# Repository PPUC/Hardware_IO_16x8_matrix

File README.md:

# Switch Matrix PCB for PPUC Project
This is the hardware for a 16x8 switch matrix card which was designed for the PPUC pinball project, but can be useful in other applications as well. The intentionally usecase is to connect an original equipped pinball playfield (including cable harness and diodes). Normally I'd prefer direct switches but if all the switches and cables and diodes are in place already, it is useful to connect the switch matrix directly. The board can also be used for 16 direct inputs and 8 low power signal-outputs (no matrix).  
It is designed for being low cost and functional for experimental use.  
Not everything is tested nor does it fulfill EMC or any other specifications.  
Use at your own risk!
To make use of anything of this project a basic understanding of electronics and programming is necessary. Nothing of it is "plug and play". I'm surely not liable for any damage to assemblies, pinball machines or even persons.

<!---
## Picture of the Board

-->

## Name
IO_16x8_matrix as it has 16 inputs and 8 signal-outputs to form a 16x8 switch matrix but could also be used as direct inputs and low power outputs. Actually it has an additional high speed output (see "Special Output" below).  

## Power Supply
The IO card must be supplied by 5 V (+-0.5 V). In the circuit this is named 5V_IN.

## Controller
A RP2040 is used for it's cost/performance ratio. It is the same controller that is used in the Raspberry Pi Pico.

## Communication Interfaces
* RS_485: main communication interface for controlling the outputs. Usually connected to a host interface like a PC or Raspberry Pi or similar.
* USB C: for programming, debug and flashing
* Serial Wire: alternative for programming, debug and flashing

## Switches (on board)
* Reset: hardware reset for controller (RP2040)
* Boot: if active, the board connects to a PC like an USB stick. Usually used for programming the code into the flash memory on the board.
* DIP-switches: usually used to select an address for RS485 (16 combinations)

## Signal Outputs
There are 8 outputs that can be set to 5 V or GND. They are intended to drive the switch matrix (column at WPC, row at S.A.M.). The 5 V signal is derived from the 5 V supply by a 1 kOhm pull up resistor. Therefore it is only good for signaling, not for power load. If used as a matrix please be aware that every switch must have a diode in series.

## Inputs
There are 16 inputs intended to receive the switch status of the matrix (row at WPC, column at S.A.M.). They are pulled up to 5 V and switch at a voltage of about 1.9 V. The inputs are made for low active signals (switched to GND). If used as a matrix please be aware that every switch must have a diode in series.

## Special Output
One special output is available for high speed signals. The voltage is 5 V, it is a push pull output that can drive a current up to 8 mA. It can be used to e.g. control a WS2812 LED strip.

## Connectors
There are pads for connectors that fit S.A.M. systems and also WPC systems. The pinning of the returns (rows at WPC) is unfortunately vice versa to S.A.M. so the connector of the original WPC cable harness has to be rotated by 180° (cables go to the inner side of PCB).

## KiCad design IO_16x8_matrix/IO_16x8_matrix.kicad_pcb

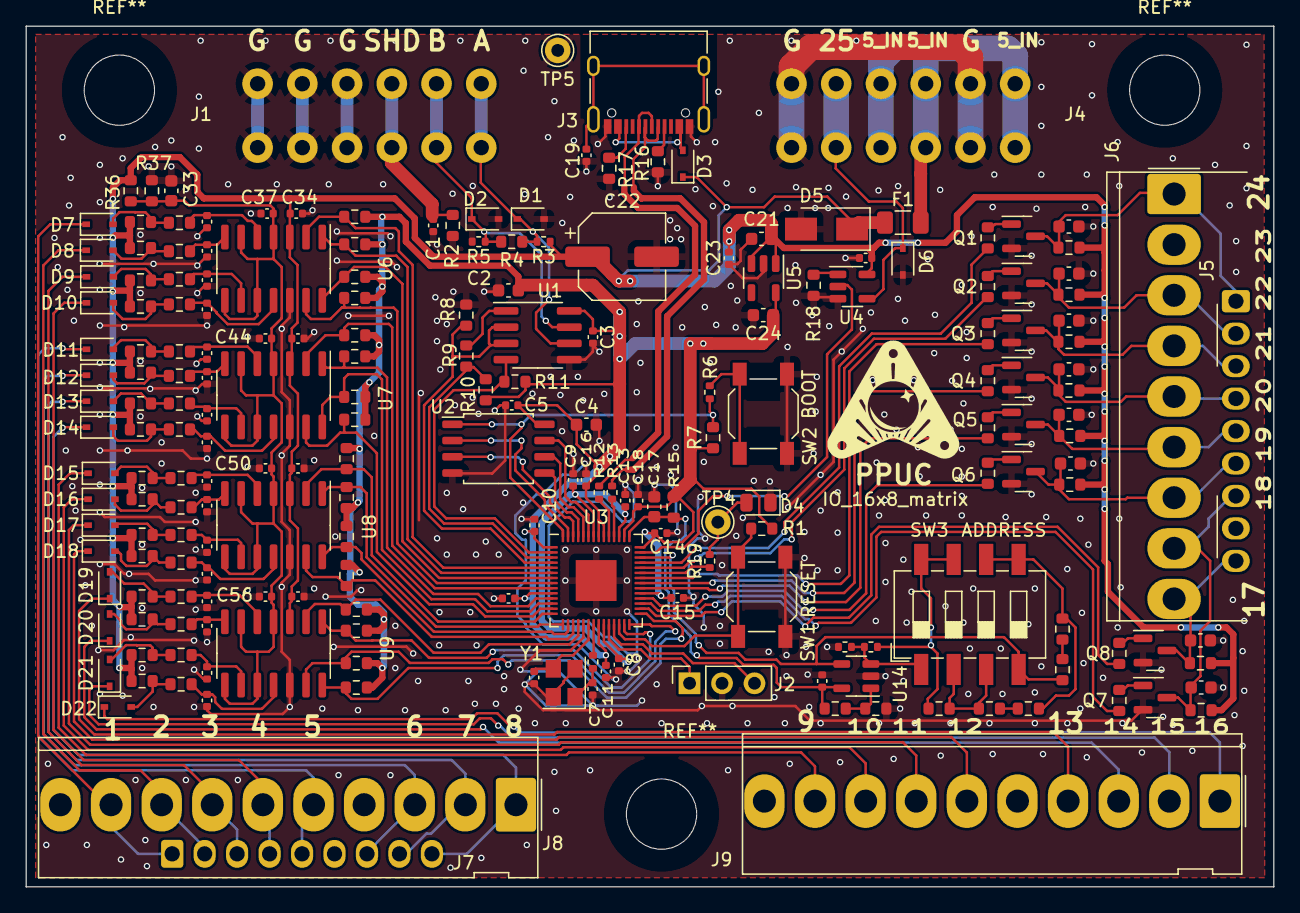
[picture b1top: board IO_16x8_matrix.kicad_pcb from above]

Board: 2 copper layers, 97.6 x 67.3 mm, 208 parts (0 on the bottom side), 136 nets.

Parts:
C1, C3, C5, C8, C9, C10, C11, C12, C14, C15, C16, C19, C20, C23, C34, C35, C36, C37, C38, C39, C40, C41, C42, C43, C44, C45, C46, C47, C48, C49, C50, C51, C52, C53, C54, C55, C56, C57, C58: 100n; C_0402_1005Metric
C2, C4, C17, C21, C24, C33: 10u; C_0603_1608Metric
C6, C7: 27pF; C_0402_1005Metric
C13, C18: 1u; C_0402_1005Metric
C22: 100µ 35V; CP_Elec_6.3x7.7
C25, C26, C27, C28, C29, C30, C31, C32: 10n; C_0603_1608Metric
D1, D2: SD15; D_SOD-323
D3: 1A; D_SOD-323
D4: LED gn; LED_0805_2012Metric
D5: SMAJ5.0; D_SMA
D6: SD05; D_SOD-323
D7, D8, D9, D10, D11, D12, D13, D14, D15, D16, D17, D18, D19, D20, D21, D22: 1N4148WS; D_SOD-323
F1: T500mA,<0.3Ω; Fuse_1206_3216Metric
J1, J4: Conn_01x06; Terminal_Block_RTMPin
J2: nmount SW Debug; PinSocket_1x03_P2.54mm_Vertical
J3: USB_C_Receptacle_USB2.0; USB_C_Receptacle_XKB_U262-16XN-4BVC11
J5, J7: Conn_01x09; Molex_KK-254_AE-6410-09A_1x09_P2.54mm_Vertical
J6: Conn_01x09; Molex_KK-396_5273-09A_1x09_P3.96mm_Vertical
J8, J9: Conn_01x10; Molex_KK-396_5273-10A_1x10_P3.96mm_Vertical
Q1, Q2, Q3, Q4, Q5, Q6, Q7, Q8: MMBT3904; SOT-23
R1, R7, R8, R10, R11, R18, R38, R39, R44, R45, R50, R51, R65, R66, R71, R72, R77, R78, R83, R84, R89, R90: 10k; R_0603_1608Metric
R2, R15, R40, R41, R46, R47, R52, R53, R67, R68, R73, R74, R79, R80, R85, R86, R91, R92: 100R; R_0603_1608Metric
R3, R5, R6, R14, R19, R58, R62: 1k; R_0402_1005Metric
R4: 120R; R_0603_1608Metric
R9: 0; R_0603_1608Metric
R12, R13: 27; R_0402_1005Metric
R16, R17: 5k1; R_0603_1608Metric
R20, R21, R22, R23, R24, R25, R26, R27, R28, R29, R30, R31, R32, R33, R34, R35, R42, R43, R48, R49, R54, R55, R69, R70, R75, R76, R81, R82, R87, R88, R93, R94: 1k; R_0603_1608Metric
R36, R37, R57, R60, R61, R64: 2k; R_0603_1608Metric
R56: 33k; R_0603_1608Metric
R59: 5k; R_0603_1608Metric
R63: 3k; R_0603_1608Metric
SW1: Reset; SW_SPST_SKQG_WithStem
SW2: Boot; SW_SPST_SKQG_WithStem
SW3: ADDRESS; SW_DIP_SPSTx04_Slide_6.7x11.72mm_W8.61mm_P2.54mm_LowProfile
TP4: TP_LED; Pin_D1.0mm_L10.0mm
TP5: TP_GND; Pin_D1.0mm_L10.0mm
U1: ADM3483; SOIC-8_3.9x4.9mm_P1.27mm
U2: W25Q128JVSIQ; SOIC-8_5.23x5.23mm_P1.27mm
U3: RP2040; QFN-56-1EP_7x7mm_P0.4mm_EP3.2x3.2mm
U4: SN74AHCT1G125; SOT-23-5
U5: AP2112K-3.3; SOT-23-5
U6, U7, U8, U9: LM339; SOIC-14_3.9x8.7mm_P1.27mm
U14: LMV321; SOT-23-5
Y1: 12MHz,18pF; Crystal_SMD_3225-4Pin_3.2x2.5mm

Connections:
+3V3: C2.1, C3.1, C4.1, C5.1, C10.1, C11.1, C12.1, C14.1, C15.1, C16.1, C18.1, C24.1, R1.2, R7.1, R10.1, R11.1, R15.1, R38.1, R39.1, R44.1, R45.1, R50.1, R51.1, R65.1, R66.1, R71.1, R72.1, R77.1, R78.1, R83.1, R84.1, R89.1, R90.1, U1.8 (VCC), U2.8 (VCC), U3.1 (IOVDD), U3.10 (IOVDD), U3.22 (IOVDD), U3.33 (IOVDD), U3.42 (IOVDD), U3.44 (VREG_IN), U3.48 (USB_VDD), U3.49 (IOVDD), U5.5 (VOUT)
+5V: C20.1, C21.1, C22.1, C23.1, C34.1, C40.1, C47.1, C53.1, D3.1 (K), D5.1 (K), F1.1, R3.1, R24.1, R25.1, R26.1, R27.1, R32.1, R33.1, R34.1, R35.1, R36.1, R42.1, R43.1, R48.1, R49.1, R54.1, R55.1, R69.1, R70.1, R75.1, R76.1, R81.1, R82.1, R87.1, R88.1, R93.1, R94.1, U4.5 (VCC), U5.1 (VIN), U5.3 (EN), U6.3 (V+), U7.3 (V+), U8.3 (V+), U9.3 (V+)
/1V1: C8.1, C9.1, C13.1, U3.23 (DVDD), U3.45 (VREG_VOUT), U3.50 (DVDD)
/3V3A: C17.1, C42.1, R15.2, R56.1, U3.43 (ADC_AVDD), U14.5 (V+)
/5V_IN: F1.2, J4.1, J4.3, J4.4
/485_DE: R8.2, U1.2 (~RE), U1.3 (DE), U3.4 (GPIO2)
/485_RX: R9.2, R10.2, U3.3 (GPIO1)
/485_TX: R11.2, U1.4 (DI), U3.2 (GPIO0)
/A: D1.1 (K), J1.1, R3.2, R4.1, U1.6 (A)
/B: D2.1 (K), J1.2, R4.2, R5.1, U1.7 (B)
/Driver8/D1: C25.1, J5.1, J6.1, Q1.3 (C), R24.2
/Driver8/D2: C26.1, J5.2, J6.3, Q2.3 (C), R25.2
/Driver8/D3: C27.1, J5.3, J6.4, Q3.3 (C), R26.2
/Driver8/D4: C28.1, J5.4, J6.5, Q4.3 (C), R27.2
/Driver8/D5: C29.1, J5.5, J6.6, Q5.3 (C), R32.2
/Driver8/D6: C30.1, J5.6, J6.7, Q6.3 (C), R33.2
/Driver8/D7: C31.1, J5.7, J6.8, Q7.3 (C), R34.2
/Driver8/D8: C32.1, J5.9, J6.9, Q8.3 (C), R35.2
/In16/T1: D7.1 (K), J7.1, J8.9
/In16/T2: D8.1 (K), J7.2, J8.8
/In16/T3: D9.1 (K), J7.3, J8.7
/In16/T4: D10.1 (K), J7.4, J8.6
/In16/T5: D11.1 (K), J7.5, J8.5
/In16/T6: D12.1 (K), J7.7, J8.3
/In16/T7: D13.1 (K), J7.8, J8.2
/In16/T8: D14.1 (K), J7.9, J8.1
/In16/T9: D15.1 (K), J9.9
/In16/T10: D16.1 (K), J9.8
/In16/T11: D17.1 (K), J9.7
/In16/T12: D18.1 (K), J9.6
/In16/T13: D19.1 (K), J9.4
/In16/T14: D20.1 (K), J9.3
/In16/T15: D21.1 (K), J9.2
/In16/T16: D22.1 (K), J9.1
/In16/V_SWITCH: C33.1, C37.1, C44.1, C50.1, C56.1, R36.2, R37.1, U6.4 (-), U6.6 (-), U6.8 (-), U6.10 (-), U7.4 (-), U7.6 (-), U7.8 (-), U7.10 (-), U8.4 (-), U8.6 (-), U8.8 (-), U8.10 (-), U9.4 (-), U9.6 (-), U9.8 (-), U9.10 (-)
/In_1: R38.2, U3.5 (GPIO3), U6.2
/In_2: R39.2, U3.6 (GPIO4), U6.1
/In_3: R44.2, U3.7 (GPIO5), U6.14
/In_4: R45.2, U3.8 (GPIO6), U6.13
/In_5: R50.2, U3.9 (GPIO7), U7.2
/In_6: R51.2, U3.11 (GPIO8), U7.1
/In_7: R65.2, U3.12 (GPIO9), U7.14
/In_8: R66.2, U3.13 (GPIO10), U7.13
/In_9: R71.2, U3.14 (GPIO11), U8.2
/In_10: R72.2, U3.15 (GPIO12), U8.1
/In_11: R77.2, U3.16 (GPIO13), U8.14
/In_12: R78.2, U3.17 (GPIO14), U8.13
/In_13: R83.2, U3.18 (GPIO15), U9.2
/In_14: R84.2, U3.27 (GPIO16), U9.1
/In_15: R89.2, U3.28 (GPIO17), U9.14
/In_16: R90.2, U3.29 (GPIO18), U9.13
/Out_1: R20.1, U3.39 (GPIO27_ADC1)
/Out_2: R21.1, U3.38 (GPIO26_ADC0)
/Out_3: R22.1, U3.36 (GPIO24)
/Out_4: R23.1, U3.35 (GPIO23)
/Out_5: R28.1, U3.34 (GPIO22)
/Out_6: R29.1, U3.32 (GPIO21)
/Out_7: R30.1, U3.31 (GPIO20)
/Out_8: R31.1, U3.30 (GPIO19)
/Out_S: D6.1 (K), J4.5, U4.4
/Out_Special: U3.41 (GPIO29_ADC3), U4.2
/Q_SCLK: U2.6 (CLK), U3.52 (QSPI_SCLK)
/Q_nCS: R6.2, R7.2, U2.1 (~CS), U3.56 (QSPI_SS)
/SHD: C1.1, J1.3, R2.1
/USB_D+: J3.A6 (D+), J3.B6 (D+), R12.1
/USB_D-: J3.A7 (D-), J3.B7 (D-), R13.1
/V_addr: R59.1, SW3.4, U3.40 (GPIO28_ADC2), U14.4
/nReset: R1.1, SW1.2, U3.26 (RUN)
GND: C1.2, C2.2, C3.2, C4.2, C5.2, C6.1, C7.1, C8.2, C9.2, C10.2, C11.2, C12.2, C13.2, C14.2, C15.2, C16.2, C17.2, C18.2, C19.2, C20.2, C21.2, C22.2, C23.2, C24.2, C25.2, C26.2, C27.2, C28.2, C29.2, C30.2, C31.2, C32.2, C33.2, C34.2, C35.2, C36.2, C37.2, C38.2, C39.2, C40.2, C41.2, C42.2, C43.2, C44.2, C45.2, C46.2, C47.2, C48.2, C49.2, C50.2, C51.2, C52.2, C53.2, C54.2, C55.2, C56.2, C57.2, C58.2, D1.2 (A), D2.2 (A), D4.1 (K), D5.2 (A), D6.2 (A), J1.4, J1.5, J1.6, J2.2, J3.A1 (GND), J3.A12 (GND), J3.B1 (GND), J3.B12 (GND), J4.2, J4.6, Q1.2 (E), Q2.2 (E), Q3.2 (E), Q4.2 (E), Q5.2 (E), Q6.2 (E), Q7.2 (E), Q8.2 (E), R2.2, R5.2, R8.1, R16.2, R17.2, R18.2, R37.2, R57.2, R58.2, SW1.1, SW2.1, TP5.1, U1.5 (GND), U2.4 (GND), U3.19 (TESTEN), U3.57 (GND), U4.3 (GND), U5.2 (GND), U6.12 (V-), U7.12 (V-), U8.12 (V-), U9.12 (V-), U14.2 (V-), Y1.2, Y1.4
unnamed: C6.2, U3.20 (XIN), Y1.3
unnamed: C7.2, R14.1, Y1.1
unnamed: C19.1, J3.S1 (SHIELD)
unnamed: C35.1, R40.1, U6.5 (+)
unnamed: C36.1, R41.1, U6.7 (+)
unnamed: C38.1, R46.1, U6.9 (+)
unnamed: C39.1, R47.1, U6.11 (+)
unnamed: C41.1, R52.1, U7.5 (+)
unnamed: C43.1, R53.1, U7.7 (+)
unnamed: C45.1, R67.1, U7.9 (+)
unnamed: C46.1, R68.1, U7.11 (+)
unnamed: C48.1, R73.1, U8.5 (+)
unnamed: C49.1, R74.1, U8.7 (+)
unnamed: C51.1, R79.1, U8.9 (+)
unnamed: C52.1, R80.1, U8.11 (+)
unnamed: C54.1, R85.1, U9.5 (+)
unnamed: C55.1, R86.1, U9.7 (+)
unnamed: C57.1, R91.1, U9.9 (+)
unnamed: C58.1, R92.1, U9.11 (+)
unnamed: D3.2 (A), J3.A4 (VBUS), J3.A9 (VBUS), J3.B4 (VBUS), J3.B9 (VBUS)
unnamed: D4.2 (A), R19.2, TP4.1
unnamed: D7.2 (A), R40.2, R42.2
unnamed: D8.2 (A), R41.2, R43.2
unnamed: D9.2 (A), R46.2, R48.2
unnamed: D10.2 (A), R47.2, R49.2
unnamed: D11.2 (A), R52.2, R54.2
unnamed: D12.2 (A), R53.2, R55.2
unnamed: D13.2 (A), R67.2, R69.2
unnamed: D14.2 (A), R68.2, R70.2
unnamed: D15.2 (A), R73.2, R75.2
unnamed: D16.2 (A), R74.2, R76.2
unnamed: D17.2 (A), R79.2, R81.2
unnamed: D18.2 (A), R80.2, R82.2
unnamed: D19.2 (A), R85.2, R87.2
unnamed: D20.2 (A), R86.2, R88.2
unnamed: D21.2 (A), R91.2, R93.2
unnamed: D22.2 (A), R92.2, R94.2
unnamed: J2.1, U3.24 (SWCLK)
unnamed: J2.3, U3.25 (SWD)
unnamed: J3.A5 (CC1), R16.1
unnamed: J3.B5 (CC2), R17.1
unnamed: Q1.1 (B), R20.2
unnamed: Q2.1 (B), R21.2
unnamed: Q3.1 (B), R22.2
unnamed: Q4.1 (B), R23.2
unnamed: Q5.1 (B), R28.2
unnamed: Q6.1 (B), R29.2
unnamed: Q7.1 (B), R30.2
unnamed: Q8.1 (B), R31.2
unnamed: R6.1, SW2.2
unnamed: R9.1, U1.1 (RO)
unnamed: R12.2, U3.47 (USB_DP)
unnamed: R13.2, U3.46 (USB_DM)
unnamed: R14.2, U3.21 (XOUT)
unnamed: R18.1, U4.1
unnamed: R19.1, U3.37 (GPIO25)
unnamed: R56.2, R57.1, U14.1 (+)
unnamed: R58.1, R62.1, SW3.1, U14.3 (-)
unnamed: R59.2, R63.1
unnamed: R60.1, R61.1, SW3.2, SW3.3
unnamed: R60.2, R64.1
unnamed: R61.2, R62.2, SW3.7, SW3.8
unnamed: R63.2, R64.2, SW3.5, SW3.6
unnamed: U2.2 (DO(IO1)), U3.55 (QSPI_SD1)
unnamed: U2.3 (IO2), U3.54 (QSPI_SD2)
unnamed: U2.5 (DI(IO0)), U3.53 (QSPI_SD0)
unnamed: U2.7 (IO3), U3.51 (QSPI_SD3)

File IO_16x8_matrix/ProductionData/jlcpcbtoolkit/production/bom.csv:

Designator,Footprint,Quantity,Value,LCSC Part #
"C1, C10, C11, C12, C14, C15, C16, C19, C20, C23, C3, C34, C35, C36, C37, C38, C39, C40, C41, C42, C43, C44, C45, C46, C47, C48, C49, C5, C50, C51, C52, C53, C54, C55, C56, C57, C58, C8, C9",0402,39,100n,C1525
"C13, C18",0402,2,1u,C52923
"C17, C2, C21, C24, C33, C4",0603,6,10u,C19702
C22,CP_Elec_6.3x7.7,1,100µ 35V,C2836437
"C25, C26, C27, C28, C29, C30, C31, C32",0603,8,10n,C57112
"C6, C7",0402,2,27pF,C1557
"D1, D2",D_SOD-323,2,SD15,C502529
"D10, D11, D12, D13, D14, D15, D16, D17, D18, D19, D20, D21, D22, D7, D8, D9",D_SOD-323,16,1N4148WS,C2128
D3,D_SOD-323,1,1A,C191023
D4,0805,1,LED gn,C2297
D5,D_SMA,1,SMAJ5.0,C2925443
D6,D_SOD-323,1,SD05,C2972756
F1,1206,1,"T500mA,<0.3Ω",C206993
J3,USB_C_Receptacle_XKB_U262-16XN-4BVC11,1,USB_C_Receptacle_USB2.0,C709357
"Q1, Q2, Q3, Q4, Q5, Q6, Q7, Q8",SOT-23,8,MMBT3904,C20526
"R1, R10, R11, R18, R38, R39, R44, R45, R50, R51, R65, R66, R7, R71, R72, R77, R78, R8, R83, R84, R89, R90",0603,22,10k,C25804
"R12, R13",0402,2,27,C138021
"R14, R19, R3, R5, R58, R6, R62",0402,7,1k,C11702
"R15, R2, R40, R41, R46, R47, R52, R53, R67, R68, R73, R74, R79, R80, R85, R86, R91, R92",0603,18,100R,C22775
"R16, R17",0603,2,5k1,C23186
"R20, R21, R22, R23, R24, R25, R26, R27, R28, R29, R30, R31, R32, R33, R34, R35, R42, R43, R48, R49, R54, R55, R69, R70, R75, R76, R81, R82, R87, R88, R93, R94",0603,32,1k,C21190
"R36, R37, R57, R60, R61, R64",0603,6,2k,C22975
R4,0603,1,120R,C22787
R56,0603,1,33k,C4216
R59,0603,1,5k,C101077
R63,0603,1,3k,C4211
R9,0603,1,0,C21189
SW1,SW_SPST_SKQG_WithStem,1,Reset,C318884
SW2,SW_SPST_SKQG_WithStem,1,Boot,C318884
SW3,SW_DIP_SPSTx04_Slide_6.7x11.72mm_W8.61mm_P2.54mm_LowProfile,1,ADDRESS,C54950
U1,SOIC-8_3.9x4.9mm_P1.27mm,1,ADM3483,C609792
U14,SOT-23-5,1,LMV321,C7972
U2,SOIC-8_5.23x5.23mm_P1.27mm,1,W25Q128JVSIQ,C97521
U3,QFN-56-1EP_7x7mm_P0.4mm_EP3.2x3.2mm,1,RP2040,C2040
U4,SOT-23-5,1,SN74AHCT1G125,C7484
U5,SOT-23-5,1,AP2112K-3.3,C51118
"U6, U7, U8, U9",SOIC-14_3.9x8.7mm_P1.27mm,4,LM339,C179558
Y1,Crystal_SMD_3225-4Pin_3.2x2.5mm,1,"12MHz,18pF",C9002

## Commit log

2024-02-24 test
2024-02-24 initial
2024-03-24 routed
2024-03-26 opt routing
2024-03-27 prod_data
2024-03-27 readme update
2024-03-27 added csvs
2024-03-27 cleaned up
2024-09-19 added pic
2024-12-01 V1.0.0
